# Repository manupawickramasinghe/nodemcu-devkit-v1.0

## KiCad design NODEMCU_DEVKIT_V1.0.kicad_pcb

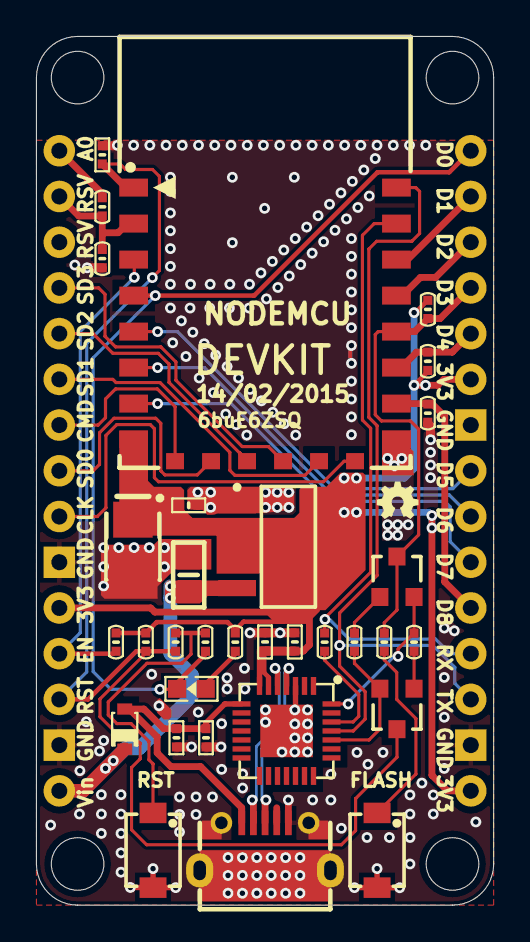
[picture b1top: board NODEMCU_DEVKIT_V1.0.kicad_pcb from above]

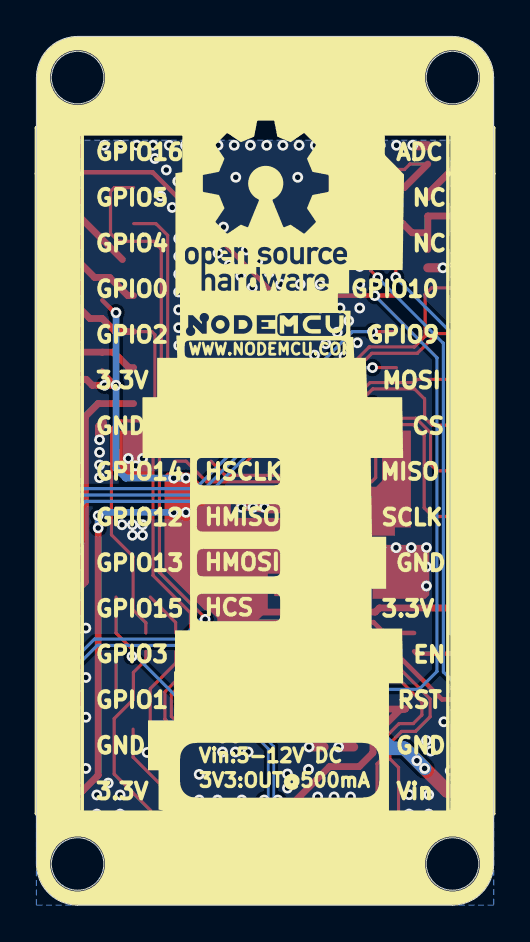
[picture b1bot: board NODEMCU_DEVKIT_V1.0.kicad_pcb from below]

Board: 2 copper layers, 25.4 x 48.3 mm, 34 parts (2 on the bottom side), 35 nets.

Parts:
C1, C4, C6: 100nF; SMT_C_0402
C2: 100uF TAJB107M006RNJ; SMT_C_Tantalum_B
C3, C5, C8: 10uF; SMT_C_0402
C7: 10uF 25V; SMT_C_0805
D1: 1N5819/SS14/S4(SOD_323); SMT_DIODE_SOD_323
J1, J2: THT_Male_P_1x15; THT_Male_P_1x15-2.54mm
LED1: BLUE; SMT_LED_0603
R1, R2, R3, R4, R5, R7, R8: 12k; SMT_R_0402
R6, R9, R11, R12: 470; SMT_R_0402
R10: 0(NC); SMT_R_0402
R13: 220k(1%); SMT_R_0402
R14: 100k(1%); SMT_R_0402
S1: KEY_RST/USER; SMT_SW_PTS_820
S2: KEY_FLASH; SMT_SW_PTS_820
U1: ESP_12_E; ESP_12_E_L
U2: CP2102
U3: USB_Micro_5S_B; USB_MICRO_5S_B
U4: NCP1117ST33T3G; SOT-223
VT1, VT2: S8050; SMT_TRIODE_NPN

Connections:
ADC: J1.2, R13.1, R14.2, U1.2
ADC_EX: J1.1, R13.2
DTR: R7.2, U2.28, VT2.2
D_N: U2.5, U3.2
D_P: U2.4, U3.3
EN: J1.12, R3.2, U1.3
GND: C1.2, C2.2, C3.2, C4.2, C5.2, C6.2, C7.2, C8.2, J1.10, J1.14, J2.7, J2.14, R5.1, R14.1, S1.2, S2.2, U1.15, U2.3, U2.29, U3.5, U3.6, U3.7, U3.8, U3.9, U4.1
GPIO0: J2.4, R1.2, R12.2, U1.18, VT2.3
GPIO2: J2.5, R2.2, U1.17
GPIO4: J2.3, U1.19
GPIO5: J2.2, U1.20
GPIO9: J1.5, U1.11
GPIO10: J1.4, U1.12
GPIO12: J2.9, U1.6
GPIO13: J2.10, U1.7
GPIO14: J2.8, U1.5
GPIO15: J2.11, R5.2, U1.16
GPIO16: J2.1, LED1.2, R10.2, U1.4
NRST: C1.1, J1.13, R4.2, R11.2, U1.1, VT1.3
NetLED1_1: LED1.1, R9.1
NetR6_1: R6.1, U2.26
NetR7_1: R7.1, VT1.1
NetR8_1: R8.1, VT2.1
NetR10_1: R10.1, R11.1, S1.1
NetR12_1: R12.1, S2.1
RTS: R8.2, U2.24, VT1.2
RXD0: J2.12, R6.2, U1.21
SPI_CLK: J1.9, U1.14
SPI_INT: J1.6, U1.13
SPI_MISO: J1.8, U1.10
SPI_MOSI: J1.7, U1.9
TXD0: J2.13, U1.22, U2.25
VDD3V3: C2.1, C3.1, C4.1, C8.1, J1.11, J2.6, J2.15, R1.1, R2.1, R3.1, R4.1, R9.2, U1.8, U2.6, U2.7, U4.2
VDD5V: C7.1, D1.2, J1.15, U4.3
VDDUSB: C5.1, C6.1, D1.1, U2.8, U3.1

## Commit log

2024-12-05 Adding KIcad edit Capable FIles
